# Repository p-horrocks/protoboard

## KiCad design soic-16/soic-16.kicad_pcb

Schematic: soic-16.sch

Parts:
C1: BLANK_8PIN; MSOP-8
C2: BLANK_16PIN; SOIC-16
C3: BLANK_5PIN; SOT-23-5
C4: BLANK_3PIN; SOT-23
P1, P2: HEADER_8X1; Header_8x1

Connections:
unnamed: C1.8, C2.1, P1.8
unnamed: C2.8, C4.3, P1.1
unnamed: C1.1, C2.16, P2.1
unnamed: C2.5, C3.3, P1.4
unnamed: C2.6, C3.2, P1.3
unnamed: C2.7, C3.1, P1.2
unnamed: C2.12, C3.4, P2.5
unnamed: C1.5, C2.4, P1.5
unnamed: C1.6, C2.3, P1.6
unnamed: C1.7, C2.2, P1.7
unnamed: C1.4, C2.13, P2.4
unnamed: C1.3, C2.14, P2.3
unnamed: C1.2, C2.15, P2.2
unnamed: C2.11, C3.5, P2.6
unnamed: C2.10, C4.1, P2.7
unnamed: C2.9, C4.2, P2.8

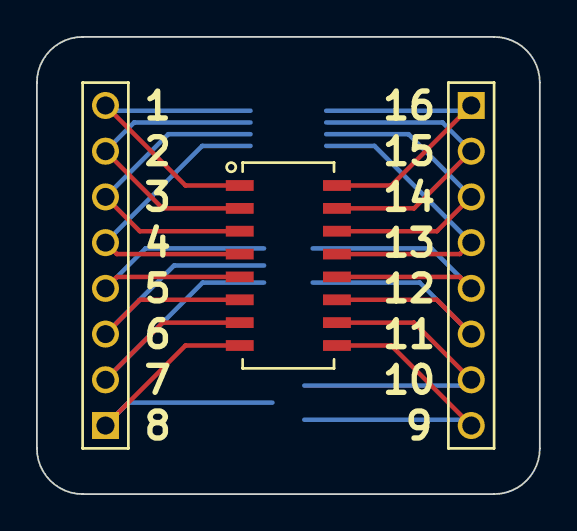
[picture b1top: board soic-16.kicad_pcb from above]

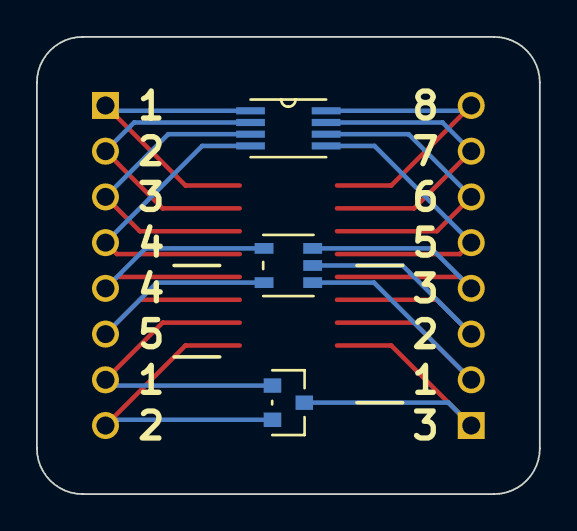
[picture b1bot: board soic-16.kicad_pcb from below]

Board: 2 copper layers, 27.9 x 25.4 mm, 6 parts (3 on the bottom side), 16 nets.

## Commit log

2016-03-13 Added schematic for soic-16 board with sot-23, sot-23-5 and msop-8 on the back
2016-03-13 Apparently save all doesn't save all
2016-03-14 Laid out soic-16 PCB
2016-03-14 Added board edge
2016-03-18 Add rouded corners
